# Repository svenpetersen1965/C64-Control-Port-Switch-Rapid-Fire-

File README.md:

# C64-Control-Port-Switch-Rapid-Fire-
This is a Control Port Switch for the Commodore C64. It provides a rapid fire function. Other than an auto fire function, it fires only as long as the fire button is pressed. And the firing is synchronized with pressing this button. The delay is <= 1msec - the human reaction time is about 300msec.

The micro controller is a (Arduino) Pro Micro. This way, no fancy tools are required for uploading the firmware (just a micro usb B cable).

Find some info on the required cable making <a href="http://tech.guitarsite.de/cable_making.html">on my website</a>

Completed project

The PCB

The guts

# Recommended Screws
Those are mentioned in the documentation.

# Component Price
The price for the components and PCB was calculated. It is 20.49€ without the 3D printed case (as of June 8th, 2020). The components can be bought cheaper, in case the Pro Micro is bought from AliExpress or Ebay (non domestic).

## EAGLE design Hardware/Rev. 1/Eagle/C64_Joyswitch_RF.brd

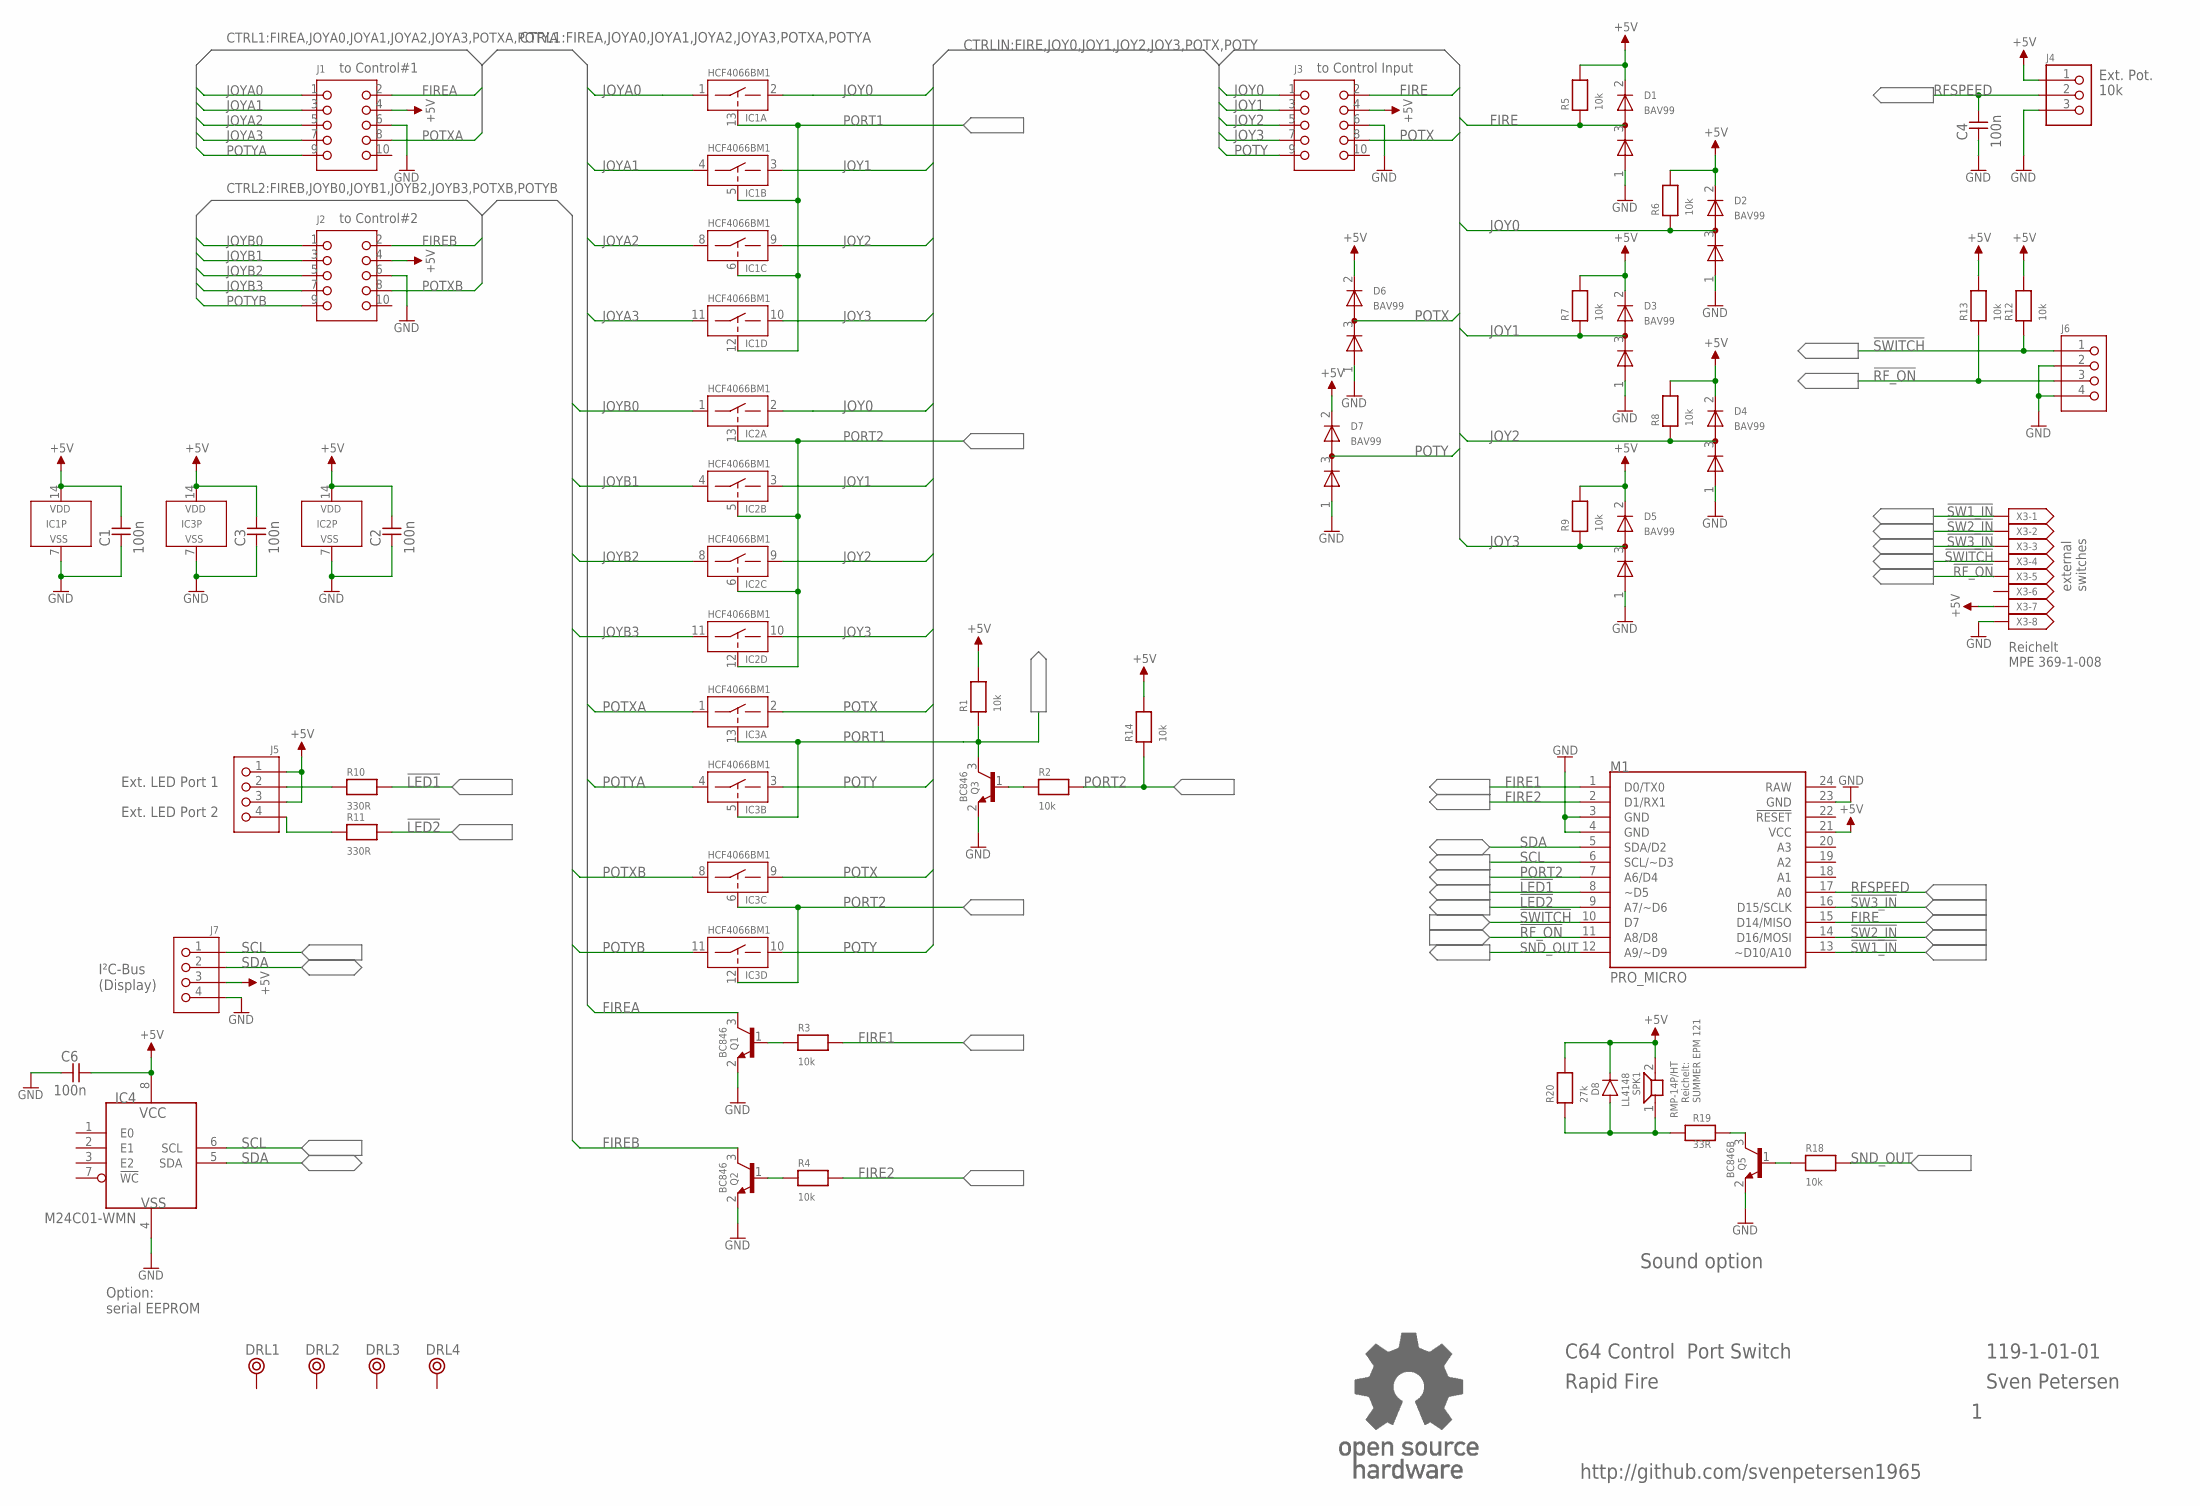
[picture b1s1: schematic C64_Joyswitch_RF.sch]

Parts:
C1, C2, C3, C4, C6: 100n; 0805
D1, D2, D3, D4, D5, D6, D7: BAV99; SOT23
D8: LL4148; SOD80C
DRL1, DRL2, DRL3, DRL4: BOHR3,1
IC1, IC2, IC3: HCF4066BM1; SO-14
IC4: M24C01-WMN; SO-08
J1, J2, J3: 2X05WV
J4: 6410-3P
J5, J6, J7: 6410-4P
M1: PRO_MICRO
Q1, Q2, Q3: BC846; SOT23
Q5: BC846B; SOT23
R1, R2, R3, R4, R5, R6, R7, R8, R9, R12, R13, R14, R18: 10k; 0805
R10, R11: 330R; 0805
R19: 33R; 0805
R20: 27k; 0805
SPK1: RMP-14P/HT
U$94: OPEN_SOURCE_HW; OPENHW
X3: 369-1-008; MICMA08B

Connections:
!LED1: M1.8 (~D5), R10.2
!LED2: M1.9 (A7/~D6), R11.2
!RF_ON: J6.3, M1.11 (A8/D8), R13.1, X3.5
!SW1_IN: M1.13 (~D10/A10), X3.1
!SW2_IN: M1.14 (D16/MOSI), X3.2
!SW3_IN: M1.16 (D15/SCLK), X3.3
!SWITCH: J6.1, M1.10 (D7), R12.1, X3.4
+5V: C1.2, C2.2, C3.2, C6.2, D1.2 (K), D2.2 (K), D3.2 (K), D4.2 (K), D5.2 (K), D6.2 (K), D7.2 (K), D8.K, IC1.14 (VDD), IC2.14 (VDD), IC3.14 (VDD), IC4.8 (VCC), J1.4, J2.4, J3.4, J4.1, J5.1, J5.3, J7.3, M1.21 (VCC), R1.2, R5.2, R6.2, R7.2, R8.2, R9.2, R12.2, R13.2, R14.2, R20.2, SPK1.2, X3.7
FIRE: D1.3 (KA), J3.2, M1.15 (D14/MISO), R5.1
FIRE1: M1.1 (D0/TX0), R3.2
FIRE2: M1.2 (D1/RX1), R4.2
FIREA: J1.2, Q1.3 (C)
FIREB: J2.2, Q2.3 (C)
GND: C1.1, C2.1, C3.1, C4.1, C6.1, D1.1 (A), D2.1 (A), D3.1 (A), D4.1 (A), D5.1 (A), D6.1 (A), D7.1 (A), IC1.7 (VSS), IC2.7 (VSS), IC3.7 (VSS), IC4.4 (VSS), J1.6, J2.6, J3.6, J4.3, J6.2, J6.4, J7.4, M1.3 (GND), M1.4 (GND), M1.23 (GND), Q1.2 (E), Q2.2 (E), Q3.2 (E), Q5.2 (E), X3.8
JOY0: D2.3 (KA), IC1.2 (B), IC2.2 (B), J3.1, R6.1
JOY1: D3.3 (KA), IC1.3 (B), IC2.3 (B), J3.3, R7.1
JOY2: D4.3 (KA), IC1.9 (B), IC2.9 (B), J3.5, R8.1
JOY3: D5.3 (KA), IC1.10 (B), IC2.10 (B), J3.7, R9.1
JOYA0: IC1.1 (A), J1.1
JOYA1: IC1.4 (A), J1.3
JOYA2: IC1.8 (A), J1.5
JOYA3: IC1.11 (A), J1.7
JOYB0: IC2.1 (A), J2.1
JOYB1: IC2.4 (A), J2.3
JOYB2: IC2.8 (A), J2.5
JOYB3: IC2.11 (A), J2.7
unnamed: Q3.1 (B), R2.1
unnamed: Q1.1 (B), R3.1
unnamed: Q2.1 (B), R4.1
unnamed: J5.2, R10.1
unnamed: J5.4, R11.1
unnamed: Q5.1 (B), R18.1
unnamed: Q5.3 (C), R19.2
unnamed: D8.A, R19.1, R20.1, SPK1.1
PORT1: IC1.5 (EN), IC1.6 (EN), IC1.12 (EN), IC1.13 (EN), IC3.5 (EN), IC3.13 (EN), Q3.3 (C), R1.1
PORT2: IC2.5 (EN), IC2.6 (EN), IC2.12 (EN), IC2.13 (EN), IC3.6 (EN), IC3.12 (EN), M1.7 (A6/D4), R2.2, R14.1
POTX: D6.3 (KA), IC3.2 (B), IC3.9 (B), J3.8
POTXA: IC3.1 (A), J1.8
POTXB: IC3.8 (A), J2.8
POTY: D7.3 (KA), IC3.3 (B), IC3.10 (B), J3.9
POTYA: IC3.4 (A), J1.9
POTYB: IC3.11 (A), J2.9
RAW: M1.24 (RAW)
RFSPEED: C4.2, J4.2, M1.17 (A0)
SCL: IC4.6 (SCL), J7.1, M1.6 (SCL/~D3)
SDA: IC4.5 (SDA), J7.2, M1.5 (SDA/D2)
SND_OUT: M1.12 (A9/~D9), R18.2

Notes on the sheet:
to Control#1
to Control#2
to Control Input
Ext. Pot.
10k
Ext. LED Port 1
Ext. LED Port 2
I²C-Bus (Display)
C64 Control Port Switch
Rapid Fire
Sven Petersen
119-1-01-01
external switches
Reichelt MPE 369-1-008
Reichelt: SUMMER EPM 121
Sound option
Option: serial EEPROM
http://github.com/svenpetersen1965

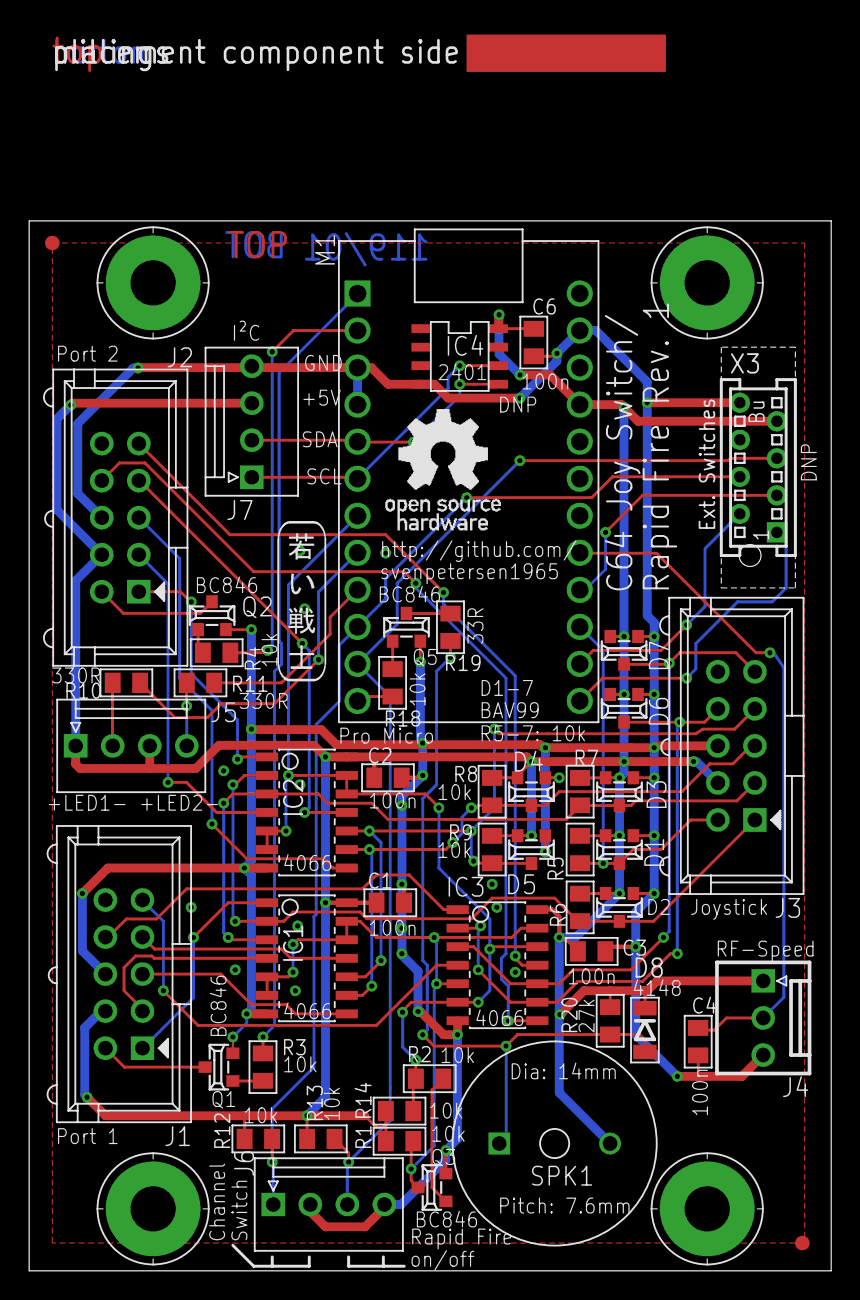
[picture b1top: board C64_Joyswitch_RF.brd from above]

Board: 2 copper layers, 55.0 x 85.1 mm, 58 parts (0 on the bottom side), 46 nets.

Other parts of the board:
U$65: 2LAYER
U$66, U$67: SMD_REF_R1MM
U$68: PCB-TITLE/
U$93: SVEN_TAG

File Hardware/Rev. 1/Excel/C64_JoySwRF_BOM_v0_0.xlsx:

C64 Joystick Switch & Rapid-Fire Rev. 0
Bill of Material Rev. 0.0
Pos. | Qty | Value | Footprint | Ref.-No. | Comment
1 | 1 | 119-2-01-00 | 2 Layer | PCB Rev. 0 | 2 layer, Cu 35µ, HASL, 72.0mm x 55.0mm, 1.6mm FR4
2 | 3 | 2x5 box connector | 2X05WV | J1, J2, J3 | e.g. Reichelt WSL 10G
3 | 3 | 10p IDC receptable, 2,54mm |  |  | e.g. Reichelt RND 205-00682
4 | 2 | 9p D-SUB (female), IDC |  | (J1), (J2) | e.g. Reichelt D-SUB BU 09FB
5 | 1 | 9p D-SUB (male), IDC |  | (J3) | e.g. Reichelt D-SUB ST 09FB
6 | 1 | 6410/22-27-2031 | 6410-3P | J4 | Molex KK Pin header, 3p., 2.54mm, e.g. Reichelt MOLEX 22272031
7 | 1 | 22-01-2031 |  | (J4) | Molex Crim Housing
8 | 1 | Potentiometer, 10k, linear, 6mm axis |  | (J4) | e.g. Reichelt PIH PC16IP061033
9 | 1 | knob for rotary axis 6 mm |  | (J4) | e.g. Reichelt KNOPF 10-150B
10 | 3 | 6410/22-27-2041 | 6410-4P | J5, J6, J7 | Molex KK Pin header, 4p., 2.54mm, e.g. Reichelt MOLEX 22272041
11 | 3 | 22-01-2041 |  | (J5), (J6), (J7) | Molex Crim Housing
12 | 15 | 2759-TL/0850-0114 |  | (J4-J7) | Molex Crim Terminal
13 | 2 | 3mm/green |  | (J5) | LED, e.g. Reichelt LED 3MM GN
14 | 2 | Miniature push button |  | (J6) | e.g. Reichelt T 113A … (different color) or arcade button (ebay)
15 | 3 | 100n | 0805 | C1, C2, C3 | ceramic capacitor 0805, 25V or better
16 | 11 | 10k | 0805 | R1, R2, R3, R4, R5, R6, R7, R8, R9, R12, R13 | chip resistor 0805, 5% or better
17 | 2 | 330R | 0805 | R10, R11 | chip resistor 0805, 5% or better
18 | 1 | 369-1-008 | MICMA08B | X3 | optional: MPE, Socket MicroMatch 1.27 mm, 2X04, straight, e.g. Reichelt MPE 369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
19 | 1 | 372-1-008 |  | (X3) | optional: MicroMatch MPE, e.g. Reichelt MPE 372-1-008
20 | 7 | BAV99 | SOT23 | D1, D2, D3, D4, D5, D6, D7 | Twin diode, SMD SOT23
21 | 3 | BC846 | SOT23 | Q1, Q2, Q3 | NPN transistor, SMD SOT23
22 | 1 | HCF4066BM1 | SO-14 | IC2 | 4066B SMD, e.g. ST-Micro or NXP, Reichelt SMD 4066
23 | 1 | M74HC241M1R | SO-20L | IC1 | 74HC241 SMD, e.g. TI, Reichelt SMD HC 241
24 | 1 | PRO_MICRO | PRO_MICRO | M1 | Micro controller module, ebay or other online shops
25 | 1 | LCD 2x16, I²C, 5V |  | (J7) | LDC Display, 2 x 16 characters, I²C, 5V supply, ebay or online shops
26 | 1 | Plastic Case |  |  | e.g. Reichelt RND 455-00959
27 | 2 | LED holder 3mm |  |  | e.g. Reichelt MONTAGERING 3MM
28 | 20cm | Wire, 0.25mm², red |  |  | for LEDs
29 | 60cm | Wire, 0.25mm², black |  |  | for LEDs and switches
30 | 8cm | shrinkable sleve |  |  | for LEDs and switches
31 | 30cm | Ribbon Cable, AWG28, 10p |  |  | For joystick and control port connections
32 | 2 | socket strips, 12p |  | (M1) | MPE 115-1-012

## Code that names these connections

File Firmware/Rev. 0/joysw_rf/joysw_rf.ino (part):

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#endif  // ifdef OLED


#define rfspeed  A0                       // potentiometer input
#define blink_time 200                    // blink time (msecs)
#define snd_time 250                      // sound time (msecs)
#define debounce 30
#define rate_cycle 250                    // display the fire rate every <rate_cycle> msecs


int fire1 = 1;   // fire port #1 (active high)
int fire2 = 0;   // fire port #2 (active high)
int port2 = 4;   // port switch #1 = low, #2 = high
int nled1 = 5;   // led port #1 (active low)
int nled2 = 6;   // led port #2 (active low)
int nswitch = 7; // channel select switch (#1 = low, #2 = high)  
int nrf_on = 8;  // rapid fire toggle switch (active low)
int snd_out = 9; // output for piezo speaker
int nfire = 14;  // fire input from joystick

// int wait_time = 500;
int channel = 2;                  // default channel is port #2
int rapid_fire = 0;               // rapid fire flag
int loop_counter = blink_time;    // some loop counter for blinking the LEDs
int rapid_fire_interval = 200;    // rapid fire interval in mili seconds
int rf_loop_counter = 200;        // loop counter for rapid fire
int previous_fire_state = 1;      // previous state of the fire button
int debounce_counter = debounce;  // counter for debouncing rf switch
int rf_toggle = 0;                // flag to let the rapid fire only toggle once before the switch is released
int blink_state = 0;              // state of the led blink (while rapid fire)
int rf_state = 1;                 // state of rapid fire, 1 = fire, 0 = not fire
int pot_value;                    // value of the potentiometer
int fire_output = HIGH;           // fire output level
int snd_counter = 0;              // sound count down
int display_counter = 0;          // display cycle coundown
int last_rate = 0;                // last displayed fire rate

void setup() {
  digitalWrite(fire1, LOW);       // initialize with low (= inactive)
  pinMode(fire1,  OUTPUT);        // fire port #1 is an output
  
  digitalWrite(fire2, LOW);       // initialize with low (= inactive)
  pinMode(fire2, OUTPUT);         // fire port #2 is an output
  
  digitalWrite(port2, HIGH);      // initialize with high (= Port #2 is selected by default)
  pinMode(port2, OUTPUT);         // this signal determins which port is used. It is an output

  digitalWrite(nled1, HIGH);      // initialize with high (= led1 is off)
  pinMode(nled1, OUTPUT);         // led port #1 is an output
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  digitalWrite(nled2, LOW );      // initialize with low (= led2 is on)
  pinMode(nled2, OUTPUT);         // led port #2 is an output
  
  pinMode(nswitch, INPUT);        // channel select switch is an input
  pinMode(nrf_on,  INPUT);        // rapid fire toggle switch is an input
  pinMode(nfire,   INPUT);        // nfire is an input
  
  tone( snd_out, 4000 );          // 1kz sound on snd_out
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          if (rapid_fire == 0) {                            // toggle rapid fire mode
            rapid_fire = 1;                                 // on
            blink_state = 0;                                // set blink state to off 
            rf_state = 1;                                   // set rf state: fire immideately
            loop_counter = rapid_fire_interval;             // initialize loop_counter
            snd_counter = snd_time;                         // start delay for sound
            tone( snd_out, 4000 );                          // Tone on
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              digitalWrite( nled2, LOW );                  // switch on LED of Port#2
            }
          }
          rf_toggle = 1;                                   // inhibit further toggling until switch was released
        }
      }
   }
   else {
     debounce_counter = debounce;                           // reset debounce counter
     rf_toggle = 0;                                         // reset rf_toggle (allow next toggle of rapid fire state)
   }

   // blink the channel LED if rapid fire is on
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
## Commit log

2020-03-20 small fix
2020-06-09 Replaced the obsolete Molex, Calculation
    The cheaper KF2510 series can replace the Molex Pin header and crimp housings. This was chanced in the BOM. The component price was calculated (08.06.2020)
2020-07-08 Scope screen shots added
2020-08-08 Silk Screen Update
2020-08-17 Pick'n'place in mm and inch
2021-06-03 Label as PNG
